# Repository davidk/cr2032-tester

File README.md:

# CR2032 Battery Tester

Test your CR2032 coin cells using this breakout. Below 2.64v, the LED ceases to
light, indicating that the coin cell is nearing the end of its useful life.

## Bill of Materials

This builds 1 board. You'll get at least 3 from OSHPark.

| Quantity | Description | Digikey/Mouser Part Number | Board Placement |
| -------- | ----------- | ------------------- | --------------- |
| 1 | TPS3809L30DBVR | [296-10917-1-ND](http://www.digikey.com/product-detail/en/TPS3809L30DBVR/296-10917-1-ND) / [595-TPS3809L30DBVR](http://www.mouser.com/access/?pn=595-TPS3809L30DBVR) | Q1 |
| 1 | 20mm coin cell holder (through-hole) | [3003K-ND](http://www.digikey.com/product-detail/en/3003/3003K-ND) / [534-3003](http://www.mouser.com/access/?pn=534-3003) | Rear |
| 1 | 0603 imperial series resistor for LED | Generic value\*\* | R1 |
| 1 | 0805 imperial LED | Generic/Any type\*\*\* | D1 |

I used the following parts for these, but you should really source to your
desired quantity:

\*\* 1k 0603 resistor (from the spare parts bin, if you really want one though..
[RMCF0603JT1K00CT-ND](http://www.digikey.com/product-detail/en/RMCF0603JT1K00/RMCF0603JT1K00CT-ND).
Try another part and order a bunch for a better discount / price.)

\*\*\* Mouser
[645-598-8130-107F](http://www.mouser.com/access/?pn=645-598-8130-107F) (Orange
Dialight LED, Vf=1.7V, If=20mA)

## Fabrication

[OSHPark shared project here](https://oshpark.com/shared_projects/Qcq4ZSKX)

## License

Creative Commons CC0 1.0 Universal

## Trivia

This board is actually a mashup of Chris Gammell's and Dave Jones' projects. The
coin cell holder and layout comes from the free Getting to Blinky KiCAD
tutorial. The TI part and usage is derived from Dave Jones' µCurrent.  

The - battery contact area was inspired by Adafruit's Ultimate GPS Breakout (leaving the
purple soldermask causes the copper ENIG contact area to be in-set, preventing
an inserted battery from making proper contact).

#### Power usage

With a 1k series resistor and 0805 LED, this board uses approximately 1mA if the battery is left inserted with the LED on. Below the IC's threshold, everything takes up 9µA without the LED lit.

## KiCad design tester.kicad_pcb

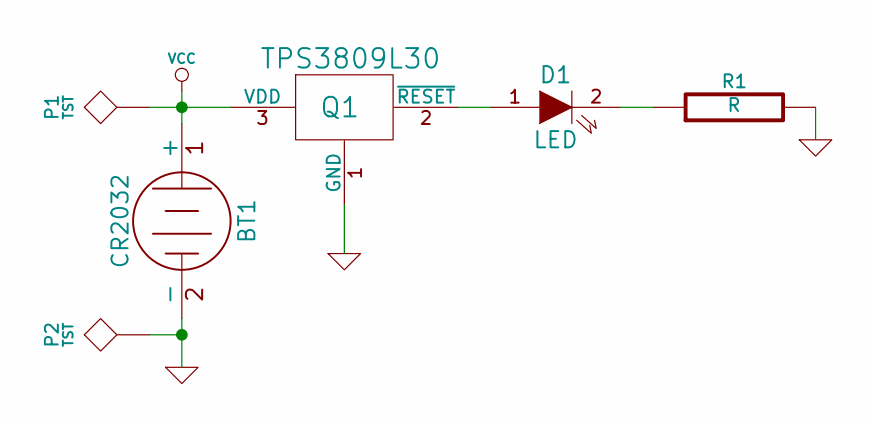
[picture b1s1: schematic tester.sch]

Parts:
BT1: CR2032
D1: LED
P1, P2: TST
Q1: TPS3809L30
R1: R

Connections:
GND: BT1.2 (-), P2.1, Q1.1 (GND), R1.2
unnamed: D1.2 (K), R1.1
unnamed: D1.1 (A), Q1.2 (~RESET)
VCC: BT1.1 (+), P1.1, Q1.3 (VDD)

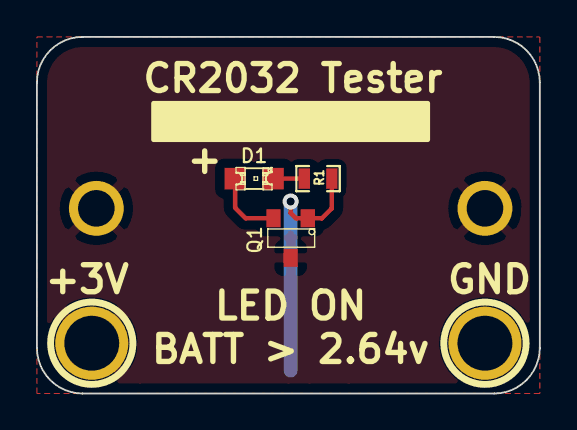
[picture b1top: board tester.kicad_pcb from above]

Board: 2 copper layers, 27.9 x 19.8 mm, 6 parts (1 on the bottom side), 4 nets.

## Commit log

2014-06-29 Add a basic gitignore for KiCad files
2014-06-29 Add board files and modules
2014-06-29 Add generated gerbers (setup for OSHPark)
2014-06-29 Fix formatting in README
2014-06-29 Update README with more information
2014-06-29 Caps for heading
2014-06-30 Battery copper contact design credit
2014-06-30 Unalign table from 80 columns
2014-06-30 Add PCB photo
2014-06-30 Fix path
2014-07-01 Add power usage statistics
    Measured with a pre-gold µCurrent and Agilent U1272A DMM
2014-07-12 New front picture
